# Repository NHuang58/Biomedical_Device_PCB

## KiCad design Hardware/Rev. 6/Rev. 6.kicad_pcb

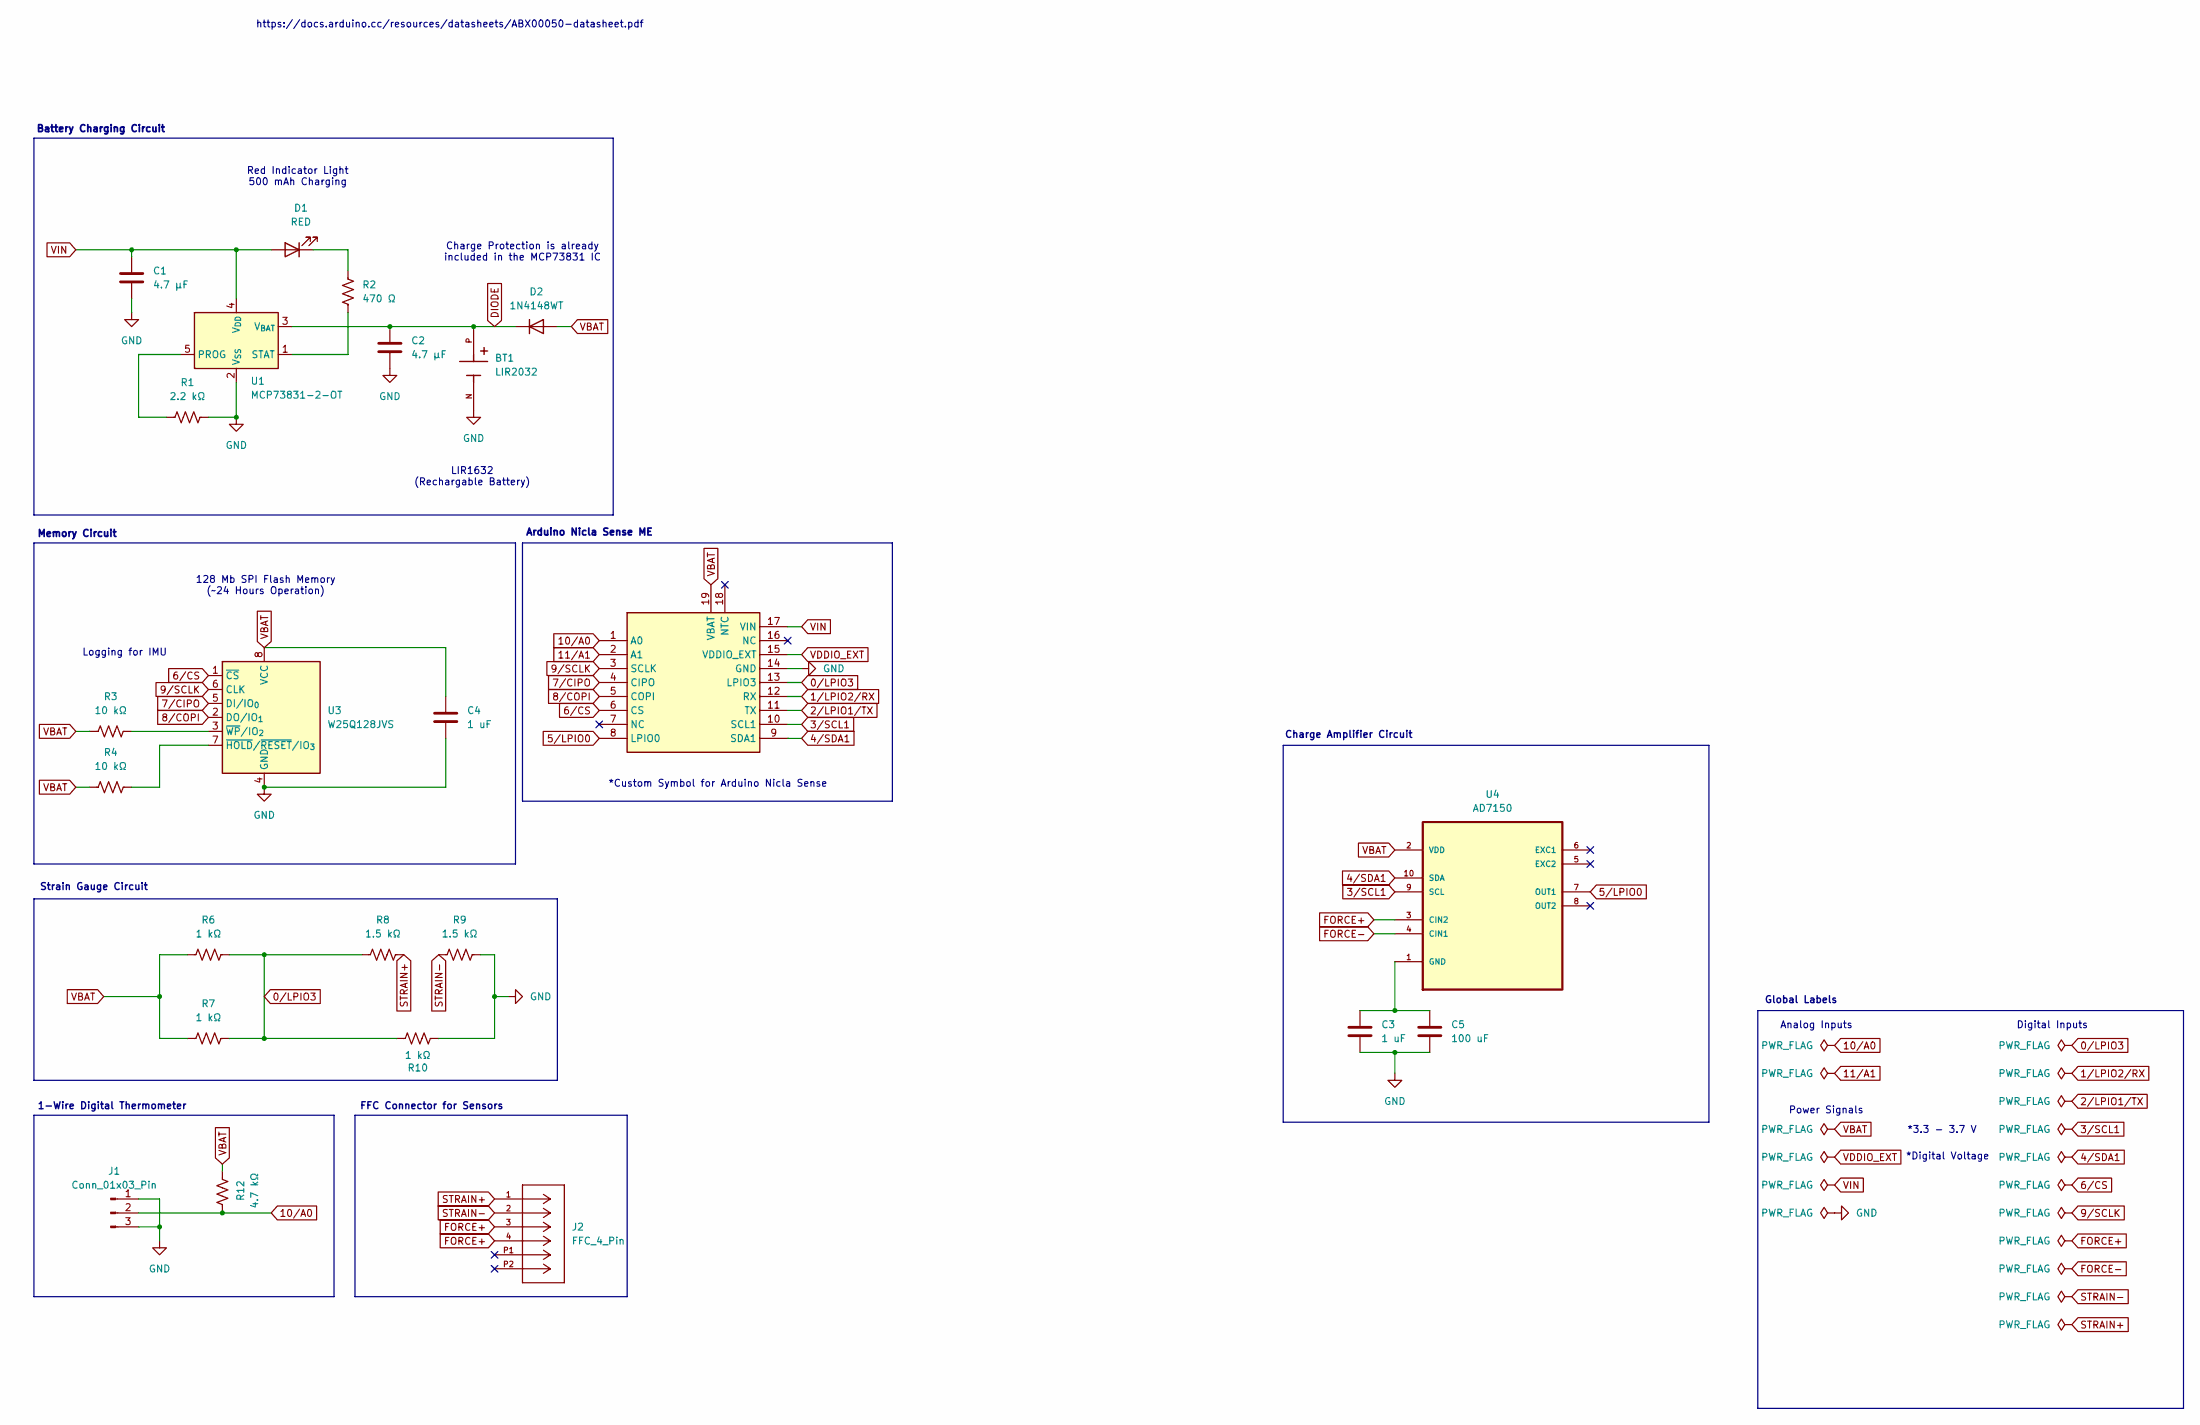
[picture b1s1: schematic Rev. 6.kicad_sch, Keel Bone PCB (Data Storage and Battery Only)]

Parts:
BT1: LIR2032; BAT_504; PARTREV H
C1, C2: 4.7 μF; C_0201_0603Metric
C3, C4: 1 uF; C_0201_0603Metric
C5: 100 uF; C_0201_0603Metric
D1: RED; D_0201_0603Metric
D2: 1N4148WT; D_SOD-523
J1: Conn_01x03_Pin; JST_ACH_BM03B-ACHSS-GAN-ETF_1x03-1MP_P1.20mm_Vertical
J2: FFC_4_Pin; MANUFACTURER_PART_NUMBER 522710479
R1: 2.2 kΩ; R_0402_1005Metric_Pad0.72x0.64mm_HandSolder
R2: 470 Ω; R_0402_1005Metric_Pad0.72x0.64mm_HandSolder
R3, R4: 10 kΩ; R_0805_2012Metric_Pad1.20x1.40mm_HandSolder
R6, R7, R10: 1 kΩ; R_0805_2012Metric_Pad1.20x1.40mm_HandSolder
R8, R9: 1.5 kΩ; R_0805_2012Metric_Pad1.20x1.40mm_HandSolder
R12: 4.7 kΩ; R_0805_2012Metric_Pad1.20x1.40mm_HandSolder
U1: MCP73831-2-OT; SOT-23-5
U2: Arduino_Nicla_Sense
U3: W25Q128JVS; SOIC-8_5.3x5.3mm_P1.27mm
U4: AD7150; MPN AD7150BRMZ

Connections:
0/LPIO3: R6.2, R7.2, R8.1, R10.1, U2.13 (LPIO3)
1/LPIO2/RX: U2.12 (RX)
2/LPIO1/TX: U2.11 (TX)
3/SCL1: U2.10 (SCL1), U4.9 (SCL)
4/SDA1: U2.9 (SDA1), U4.10 (SDA)
5/LPIO0: U2.8 (LPIO0), U4.7 (OUT1)
6/CS: U2.6 (CS), U3.1 (~CS)
7/CIPO: U2.4 (CIPO), U3.5 (DI/IO_{0})
8/COPI: U2.5 (COPI), U3.2 (DO/IO_{1})
9/SCLK: U2.3 (SCLK), U3.6 (CLK)
10/A0: J1.2, R12.1, U2.1 (A0)
11/A1: U2.2 (A1)
DIODE: BT1.P, C2.1, D2.1 (K), U1.3 (V_{BAT})
FORCE+: J2.3, J2.4, U4.3 (CIN2)
FORCE-: U4.4 (CIN1)
GND: BT1.N, C1.1, C2.2, C3.2, C4.2, C5.2, J1.1, J1.3, R1.2, R9.2, R10.2, U1.2 (V_{SS}), U2.14 (GND), U3.4 (GND)
unnamed: D1.1 (K), R2.1
unnamed: R1.1, U1.5 (PROG)
unnamed: R2.2, U1.1 (STAT)
unnamed: R4.2, U3.7 (~HOLD/~RESET/IO_{3})
unnamed: R3.2, U3.3 (~WP/IO_{2})
unnamed: C3.1, C5.1, U4.1 (GND)
STRAIN+: J2.1, R8.2
STRAIN-: J2.2, R9.1
VBAT: C4.1, D2.2 (A), R3.1, R4.1, R6.1, R7.1, R12.2, U2.19 (VBAT), U3.8 (VCC), U4.2 (VDD)
VDDIO_EXT: U2.15 (VDDIO_EXT)
VIN: C1.2, D1.2 (A), U1.4 (V_{DD}), U2.17 (VIN)

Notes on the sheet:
*Custom Symbol for Arduino Nicla Sense
*Digital Voltage
1-Wire Digital Thermometer
Charge Protection is already included in the MCP73831 IC
Global Labels
https://docs.arduino.cc/resources/datasheets/ABX00050-datasheet.pdf
Analog Inputs
*3.3 - 3.7 V
LIR1632 (Rechargable Battery)
128 Mb SPI Flash Memory (~24 Hours Operation)
Digital Inputs
Logging for IMU
Charge Amplifier Circuit
Memory Circuit
Strain Gauge Circuit
Battery Charging Circuit
Arduino Nicla Sense ME
FFC Connector for Sensors
Power Signals
Red Indicator Light 500 mAh Charging

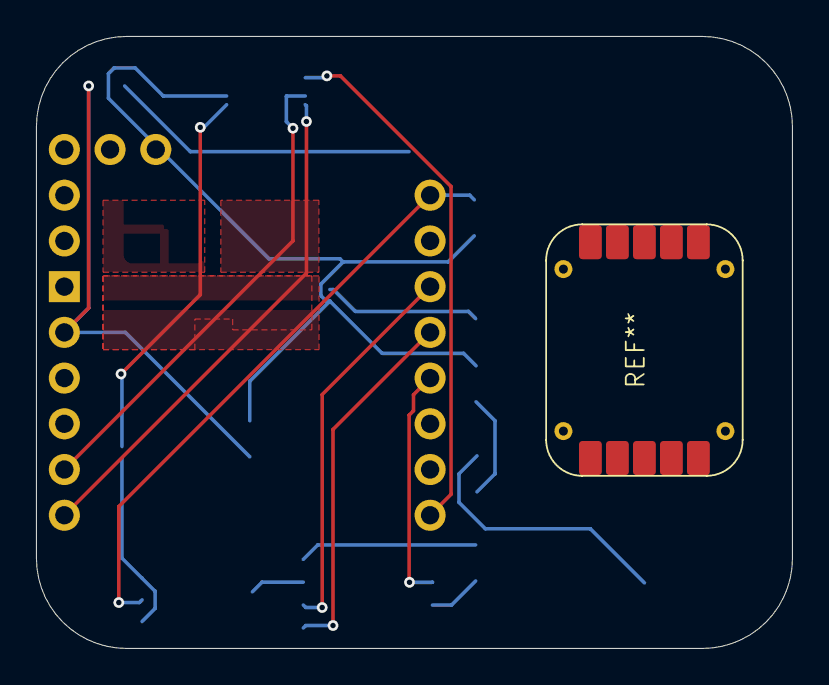
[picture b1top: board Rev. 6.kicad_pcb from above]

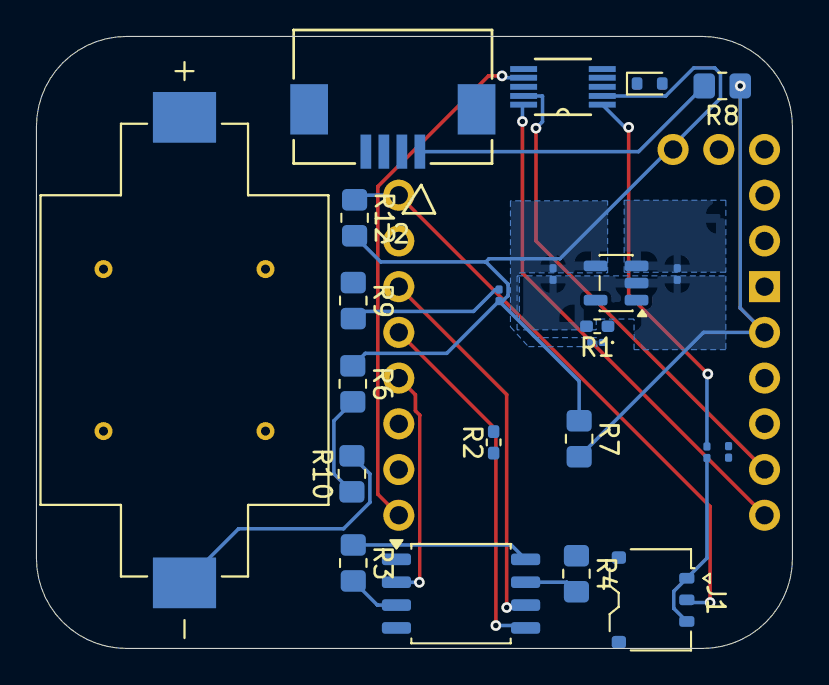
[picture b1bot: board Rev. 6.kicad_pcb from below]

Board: 2 copper layers, 42.0 x 34.0 mm, 24 parts (24 on the bottom side), 22 nets.

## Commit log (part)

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2025-09-26 Started Work on Schematic
2025-10-04 Week 3
2025-10-06 Week 3 Commits
2025-10-10 Week 4 Changes
2025-10-20 Week 5 Changes
2025-10-20 Schematic Rev. 1 Finished
2025-10-24 Hardware Changes
2025-10-24 Week 7 Changes
2025-10-31 Week 9 Changes
2025-11-03 Week 10 Changes
2025-11-07 Added Presentation Slides
2025-11-17 Week 12 Changes
2025-11-21 Week 13 Changes
2025-11-25 Week 14 Changes
2025-11-28 Added GitHub Pages Content
2025-11-28 Create CNAME
2025-11-28 Update README with hosting details
    Added hosting information for the project.
2025-11-28 Changed Index.html
2025-11-28 Change index for website
2025-12-01 Week 14 Changes (2)
2025-12-06 Week 15 Changes
2025-12-11 Protection Commit
2025-12-12 Slight Changes
2025-12-19 Week 16 Changes
2025-12-22 Week 17 Changes
2026-01-19 Week 1 Changes
2026-02-02 Increase maxRecords from 1200 to 12000
2026-02-02 Changed Index
2026-02-02 Week 4
2026-02-18 Added data
2026-02-18 Weekly Meeting
2026-02-23 Week 8 Changes
2026-03-04 Added Arduino Code Folder
2026-03-04 Website Change for Data Logging
2026-05-10 Change
2026-05-21 New Software Update + Changes
2026-06-10 Week 2 Changes
